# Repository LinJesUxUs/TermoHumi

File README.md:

# TermoHumi

Thermo-hygrometer code, powered on ATMega, AHT10 sensor and 7 Segment Display.

## Overview

TermoHumi is a compact embedded firmware project for an ATmega8 microcontroller that reads temperature and humidity from an AHT10 sensor and displays the values on a multiplexed 4-digit 7-segment LED display. The display alternates between temperature (°C) and relative humidity (%) every few seconds.

## Features

- **AHT10 I2C Sensor** — high-accuracy digital temperature and humidity sensor
- **Dynamic 7-Segment Display** — 4-digit multiplexed display with timer interrupt for flicker-free output
- **Sign Handling** — supports negative temperature readings with a minus sign indicator
- **Automatic Sensor Initialization** — sends the required calibration command (0xE1, 0x08, 0x00) on startup
- **Software Reset** — fallback sensor reset if initialization fails
- **Written in C++** — class-based I2C driver with static members for minimal overhead
- **Battery** — Designed for a disposable vape batteries

## Hardware

- **MCU:** ATmega8 (internal 2 MHz RC oscillator)
- **Sensor:** AHT10 (I2C address 0x38)
- **Display:** 4-digit 7-segment LED (common cathode/anode via PNP/NPN switching)
- **Programmer:** USBasp (ISP)

### Pin Assignment

| Port | Pin | Function                |
|------|-----|-------------------------|
| PB2  |  0  | ON state signal         |
| PB3  |  0  | PWM brightness          |
| PC0  |  0  | Digit 1 select          |
| PC1  |  1  | Digit 2 select          |
| PC2  |  2  | Digit 3 select          |
| PC3  |  3  | Digit 4 select / symbol |
| PD0  |  0  | Segment A               |
| PD1  |  1  | Segment B               |
| PD2  |  2  | Segment C               |
| PD3  |  3  | Segment D               |
| PD4  |  4  | Segment E               |
| PD5  |  5  | Segment F               |
| PD6  |  6  | Segment G               |
| PD7  |  7  | Segment DP (unused)     |
| PC4  |  4  | I2C SDA                 |
| PC5  |  5  | I2C SCL                 |

> **Note:** Port B is reserved for ISP programming. Adjust pinout if using a different ATmega variant or board layout.

## Building

### Prerequisites

- `avr-g++` (AVR GCC toolchain)
- `avr-objcopy`
- `avrdude` (for flashing)
- `make`

### Compile

```bash
make
```

This produces `bin/main.hex` ready for flashing.

### Flash

```bash
make flash
```

### Verify Flash

```bash
make verification
```

### Clean

```bash
make clean      # remove object files
make fclean     # remove all build artifacts
```

## Configuration

Edit next to adjust key parameters:

```src/common.h
#define F_CPU 2000000UL       // MCU clock frequency (Hz)
```

```src/main.cpp
#define BUTTON_ADC_CHANNEL 6  // 6 for ADC6, 7 for ADC7
#define BUTTON_THRESHOLD   85 // 1/3 from 255 (8-bit conversion)
#define BRIGHTNESS_LEVELS 4
#define EEPROM_SIZE 512

#define PERIOD_SEC 4          // Seconds between temperature/humidity display toggle
#define SEGMENT_NUM 4         // Number of 7-segment digits
#define PB2_TIMEOUT_TICKS (12 * F_CPU / (64*65)) // 10 second timeout. F_CPU / (64*65) - Timer1's frequency
```

Brightness levels sets on `brightness_values` in `main.cpp`.

The I2C bus speed is calculated in `AHT10::begin()` based on `F_CPU` (default: 100 kHz).

## Code Structure

```
.
├── src/
│   ├── main.cpp          # Application entry point, display logic, timer ISR
│   ├── AHT10.h           # AHT10 sensor driver class declaration
│   ├── AHT10.cpp         # AHT10 sensor driver implementation (I2C routines)
│   └── common.h          # Global definitions and MCU-specific includes
├── Makefile              # Build system
└── README.md
```

### Key Design Decisions

- **Timer1 interrupt** handles display multiplexing at a fixed refresh rate, ensuring flicker-free output regardless of sensor read delays.
- **Sensor reads** happen synchronously in the main loop with blocking `_delay_ms(80)` after triggering a measurement — this is acceptable because the display ISR runs independently.
- **Static class members** in `AHT10` avoid the overhead of multiple sensor instances (only one sensor is expected).

## Usage

1. Connect the hardware according to the pin assignment table.
2. Build and flash the firmware.
3. On power-up, the display shows temperature in °C.
4. After `PERIOD_SEC` seconds, the display switches to relative humidity (%).
5. The cycle repeats indefinitely.

### Display Output Format

- **Temperature:** `[sign] XX` (e.g., ` 24` for +24°C, `- 5` for -5°C)
- **Humidity:** ` XX` (e.g., ` 63` for 63%)

The 4th digit (rightmost) is used for the degree/humidity symbol, 3rd (optional) minus sign.

## Troubleshooting

| Symptom                     | Possible Cause                          |
|-----------------------------|-----------------------------------------|
| Display shows garbage/flicker | Check digit/segment pin connections     |
| Sensor returns error        | Verify I2C wiring (SDA/SCL), pull-up resistors (4.7kΩ) |
| AHT10 initialization fails  | Power-cycle sensor, check `_delay_ms(75)` after init |
| Compiler errors about `i`   | Ensure `sign` check is *inside* the `for` loop in `getTempHumi()` |
| avrdude "cannot find USB"   | Check USBasp connection and udev rules  |

## License

This project is released into the public domain. Feel free to use, modify, and distribute it without restriction.

---

**Author's Note:** This project was developed as an educational exercise in AVR C++ programming, I2C communication, and interrupt-driven display multiplexing. Contributions and suggestions are welcome.

####TODO: Case model

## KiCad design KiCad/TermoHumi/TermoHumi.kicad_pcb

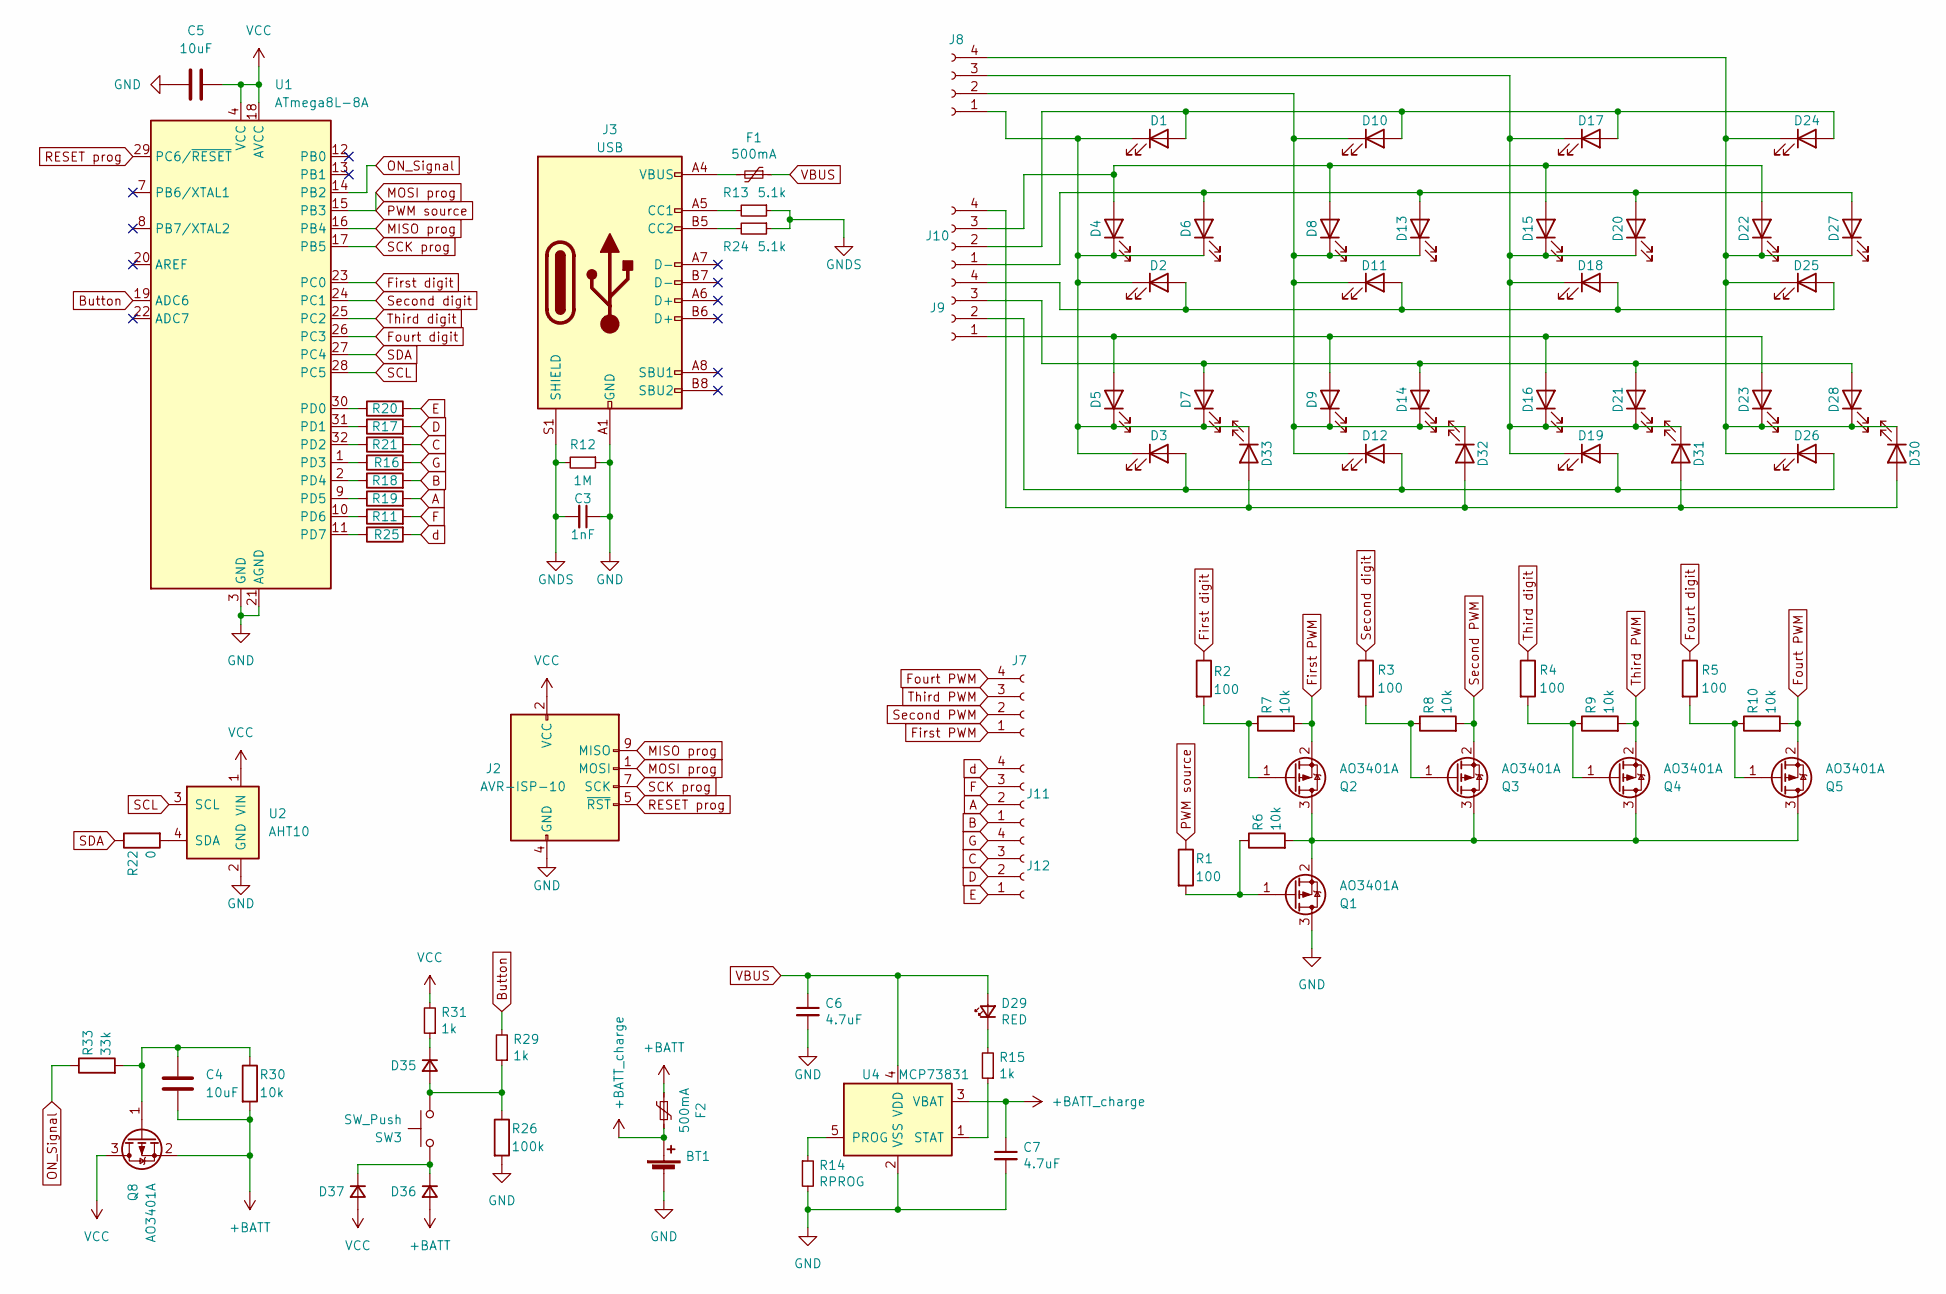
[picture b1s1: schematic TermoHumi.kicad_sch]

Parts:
BT1: Battery_Cell; PinHeader_1x02_P2.54mm_Vertical
C3: 1nF; C_0603_1608Metric_Pad1.08x0.95mm_HandSolder; LCSC C1588
C4, C5: 10uF; C_0603_1608Metric_Pad1.08x0.95mm_HandSolder
C6, C7: 4.7uF; C_0603_1608Metric_Pad1.08x0.95mm_HandSolder; LCSC C19666
D1, D2, D3, D4, D5, D6, D7, D8, D9, D10, D11, D12, D13, D14, D15, D16, D17, D18, D19, D20, D21, D22, D23, D24, D25, D26, D27, D28, D30, D31, D32, D33: LED; LED_1606_4015Metric_Pad1.42x1.75mm_HandSolder
D29: RED; LED_1606_4015Metric_Pad1.42x1.75mm_HandSolder; LCSC C2286
D35, D36, D37: 1N4148WS; D_SOD-323_HandSoldering; LCSC C57759
F1, F2: 500mA; Fuse_1206_3216Metric_Pad1.42x1.75mm_HandSolder; LCSC C355568
J2: AVR-ISP-10; PinHeader_2x05_P2.54mm_Vertical
J3: USB; USB-C_C168688
J7, J8, J9, J10, J11, J12: Conn_01x04_Socket; PinHeader_1x04_P2.54mm_Vertical
Q1, Q2, Q3, Q4, Q5, Q8: AO3401A; SOT-23
R1, R2, R3, R4, R5: 100; R_0603_1608Metric_Pad0.98x0.95mm_HandSolder
R6, R7, R8, R9, R10, R30: 10k; R_0603_1608Metric_Pad0.98x0.95mm_HandSolder
R11, R16, R17, R18, R19, R20, R21, R25: 220; R_0603_1608Metric_Pad0.98x0.95mm_HandSolder
R12: 1M; R_0603_1608Metric_Pad0.98x0.95mm_HandSolder; LCSC C22935
R13, R24: 5.1k; R_0603_1608Metric_Pad0.98x0.95mm_HandSolder; LCSC C23186
R14: RPROG; R_0603_1608Metric_Pad0.98x0.95mm_HandSolder; LCSC C22978
R15, R29, R31: 1k; R_0603_1608Metric_Pad0.98x0.95mm_HandSolder; LCSC C21190
R22: 0; R_0603_1608Metric_Pad0.98x0.95mm_HandSolder
R26: 100k; R_0603_1608Metric_Pad0.98x0.95mm_HandSolder
R33: 33k; R_0805_2012Metric_Pad1.20x1.40mm_HandSolder
SW3: SW_Push; TS-1086E_TopoR_Hack_HandSolder
U1: ATmega8L-8A; TQFP-32_7x7mm_P0.8mm
U2: AHT10; AHT10_module_x04_P2.54mm
U4: MCP73831; SOT-23-5_HandSoldering; LCSC C14879

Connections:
+BATT: C4.2, D36.2 (A), F2.2, Q8.2 (S), R30.2
+BATT_charge: BT1.1 (+), C7.1, F2.1, U4.3 (VBAT)
A: J11.2, R19.2
B: J11.1, R18.2
Button: R29.2, U1.19 (ADC6)
C: J12.3, R21.2
D: J12.2, R17.2
E: J12.1, R20.2
F: J11.3, R11.2
First PWM: J7.1, Q2.2 (S), R7.2
First digit: R2.1, U1.23 (PC0)
Fourt PWM: J7.4, Q5.2 (S), R10.2
Fourt digit: R5.1, U1.26 (PC3)
G: J12.4, R16.2
GND: BT1.2 (-), C3.1, C5.1, C6.2, C7.2, J2.4 (GND), J2.6 (GND), J2.8 (GND), J2.10 (GND), J3.A1 (GND), J3.A12 (GND), J3.B1 (GND), J3.B12 (GND), Q1.3 (D), R12.1, R14.2, R26.2, U1.3 (GND), U1.5 (GND), U1.21 (AGND), U2.2 (GND), U2.5 (GND), U4.2 (VSS)
GNDS: C3.2, J3.S1 (SHIELD), R12.2, R13.1, R24.1
MISO prog: J2.9 (MISO), U1.16 (PB4)
MOSI prog: J2.1 (MOSI), R1.1, U1.15 (PB3)
unnamed: D1.2 (A), D10.2 (A), D17.2 (A), D24.2 (A), J10.2
unnamed: D1.1 (K), D2.1 (K), D3.1 (K), D4.1 (K), D5.1 (K), D6.1 (K), D7.1 (K), D33.1 (K), J8.1
unnamed: D8.1 (K), D9.1 (K), D10.1 (K), D11.1 (K), D12.1 (K), D13.1 (K), D14.1 (K), D32.1 (K), J8.2
unnamed: D2.2 (A), D11.2 (A), D18.2 (A), D25.2 (A), J9.4
unnamed: D3.2 (A), D12.2 (A), D19.2 (A), D26.2 (A), J9.2
unnamed: D6.2 (A), D13.2 (A), D20.2 (A), D27.2 (A), J10.1
unnamed: D7.2 (A), D14.2 (A), D21.2 (A), D28.2 (A), J9.3
unnamed: D4.2 (A), D8.2 (A), D15.2 (A), D22.2 (A), J10.3
unnamed: D15.1 (K), D16.1 (K), D17.1 (K), D18.1 (K), D19.1 (K), D20.1 (K), D21.1 (K), D31.1 (K), J8.3
unnamed: D5.2 (A), D9.2 (A), D16.2 (A), D23.2 (A), J9.1
unnamed: D22.1 (K), D23.1 (K), D24.1 (K), D25.1 (K), D26.1 (K), D27.1 (K), D28.1 (K), D30.1 (K), J8.4
unnamed: D29.1 (K), R15.2
unnamed: D30.2 (A), D31.2 (A), D32.2 (A), D33.2 (A), J10.4
unnamed: D35.2 (A), R26.1, R29.1, SW3.2
unnamed: D35.1 (K), R31.1
unnamed: D36.1 (K), D37.1 (K), SW3.1
unnamed: F1.2, J3.A4 (VBUS), J3.A9 (VBUS), J3.B4 (VBUS), J3.B9 (VBUS)
unnamed: J3.A5 (CC1), R13.2
unnamed: J3.B5 (CC2), R24.2
unnamed: Q1.1 (G), R1.2, R6.1
unnamed: Q1.2 (S), Q2.3 (D), Q3.3 (D), Q4.3 (D), Q5.3 (D), R6.2
unnamed: Q2.1 (G), R2.2, R7.1
unnamed: Q3.1 (G), R3.2, R8.1
unnamed: Q4.1 (G), R4.2, R9.1
unnamed: Q5.1 (G), R5.2, R10.1
unnamed: C4.1, Q8.1 (G), R30.1, R33.2
unnamed: R20.1, U1.30 (PD0)
unnamed: R17.1, U1.31 (PD1)
unnamed: R21.1, U1.32 (PD2)
unnamed: R16.1, U1.1 (PD3)
unnamed: R18.1, U1.2 (PD4)
unnamed: R19.1, U1.9 (PD5)
unnamed: R11.1, U1.10 (PD6)
unnamed: R25.1, U1.11 (PD7)
unnamed: R22.2, U2.4 (SDA)
unnamed: R14.1, U4.5 (PROG)
unnamed: R15.1, U4.1 (STAT)
ON_Signal: R33.1, U1.14 (PB2)
RESET prog: J2.5 (~RST), U1.29 (PC6/~RESET)
SCK prog: J2.7 (SCK), U1.17 (PB5)
SCL: U1.28 (PC5), U2.3 (SCL)
SDA: R22.1, U1.27 (PC4)
Second PWM: J7.2, Q3.2 (S), R8.2
Second digit: R3.1, U1.24 (PC1)
Third PWM: J7.3, Q4.2 (S), R9.2
Third digit: R4.1, U1.25 (PC2)
VBUS: C6.1, D29.2 (A), F1.1, U4.4 (VDD)
VCC: C5.2, D37.2 (A), J2.2 (VCC), Q8.3 (D), R31.2, U1.4 (VCC), U1.6 (VCC), U1.18 (AVCC), U2.1 (VIN)
d: J11.4, R25.2

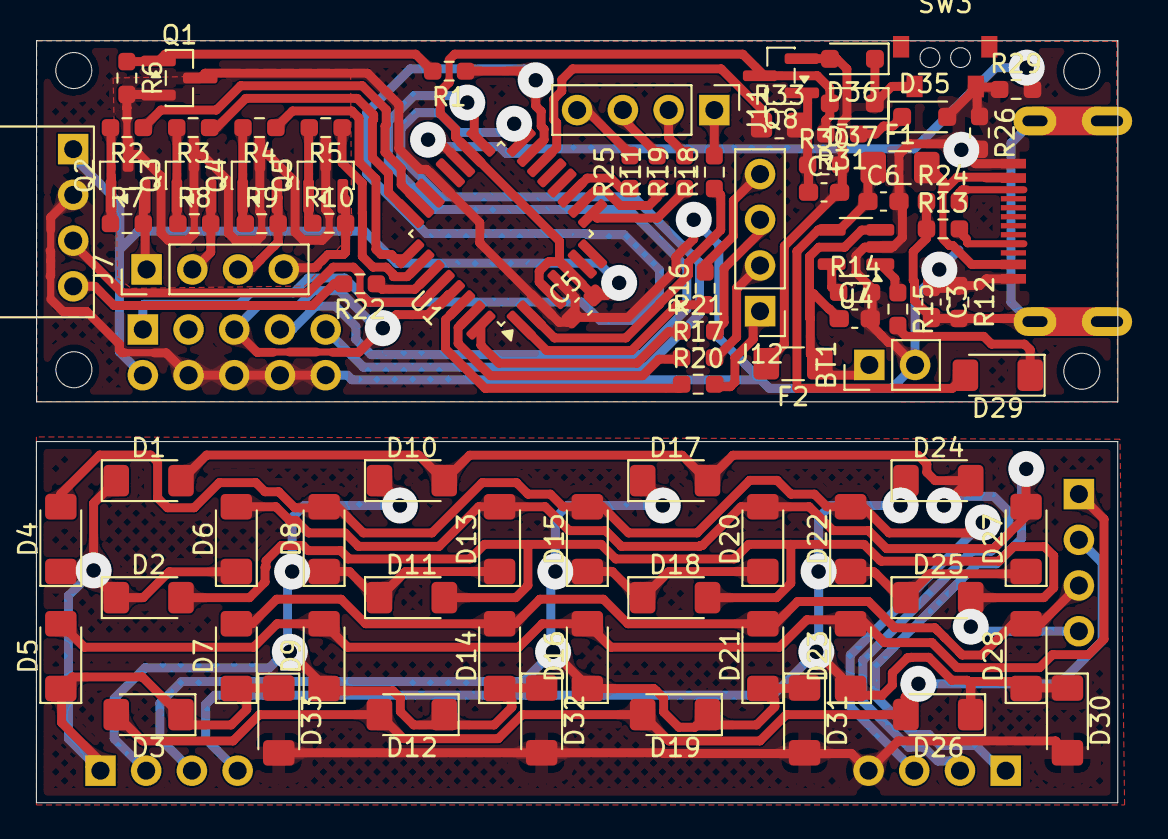
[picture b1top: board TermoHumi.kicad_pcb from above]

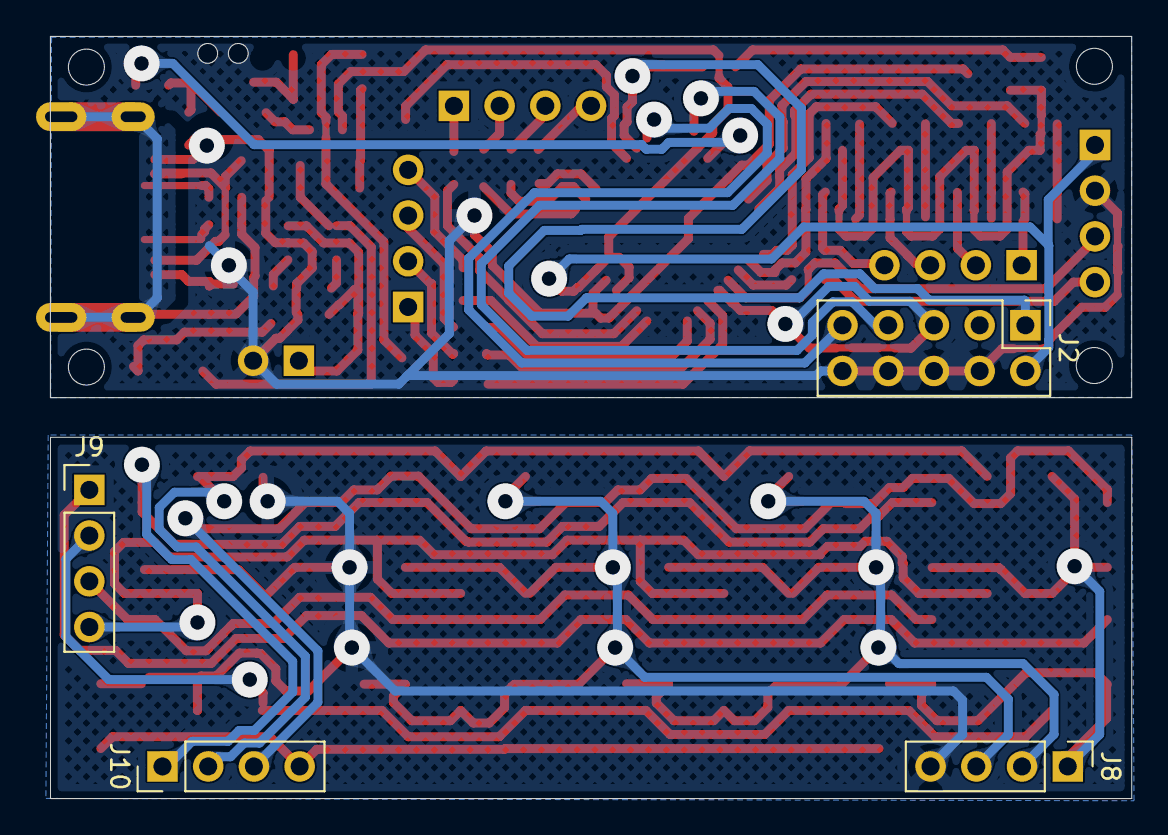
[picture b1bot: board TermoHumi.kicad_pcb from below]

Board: 2 copper layers, 60.1 x 42.3 mm, 91 parts (4 on the bottom side), 67 nets.

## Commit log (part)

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2023-12-12 class dead
